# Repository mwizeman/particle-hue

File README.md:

# particle-hue
A remote set of buttons and knobs used to control Philips Hue lights

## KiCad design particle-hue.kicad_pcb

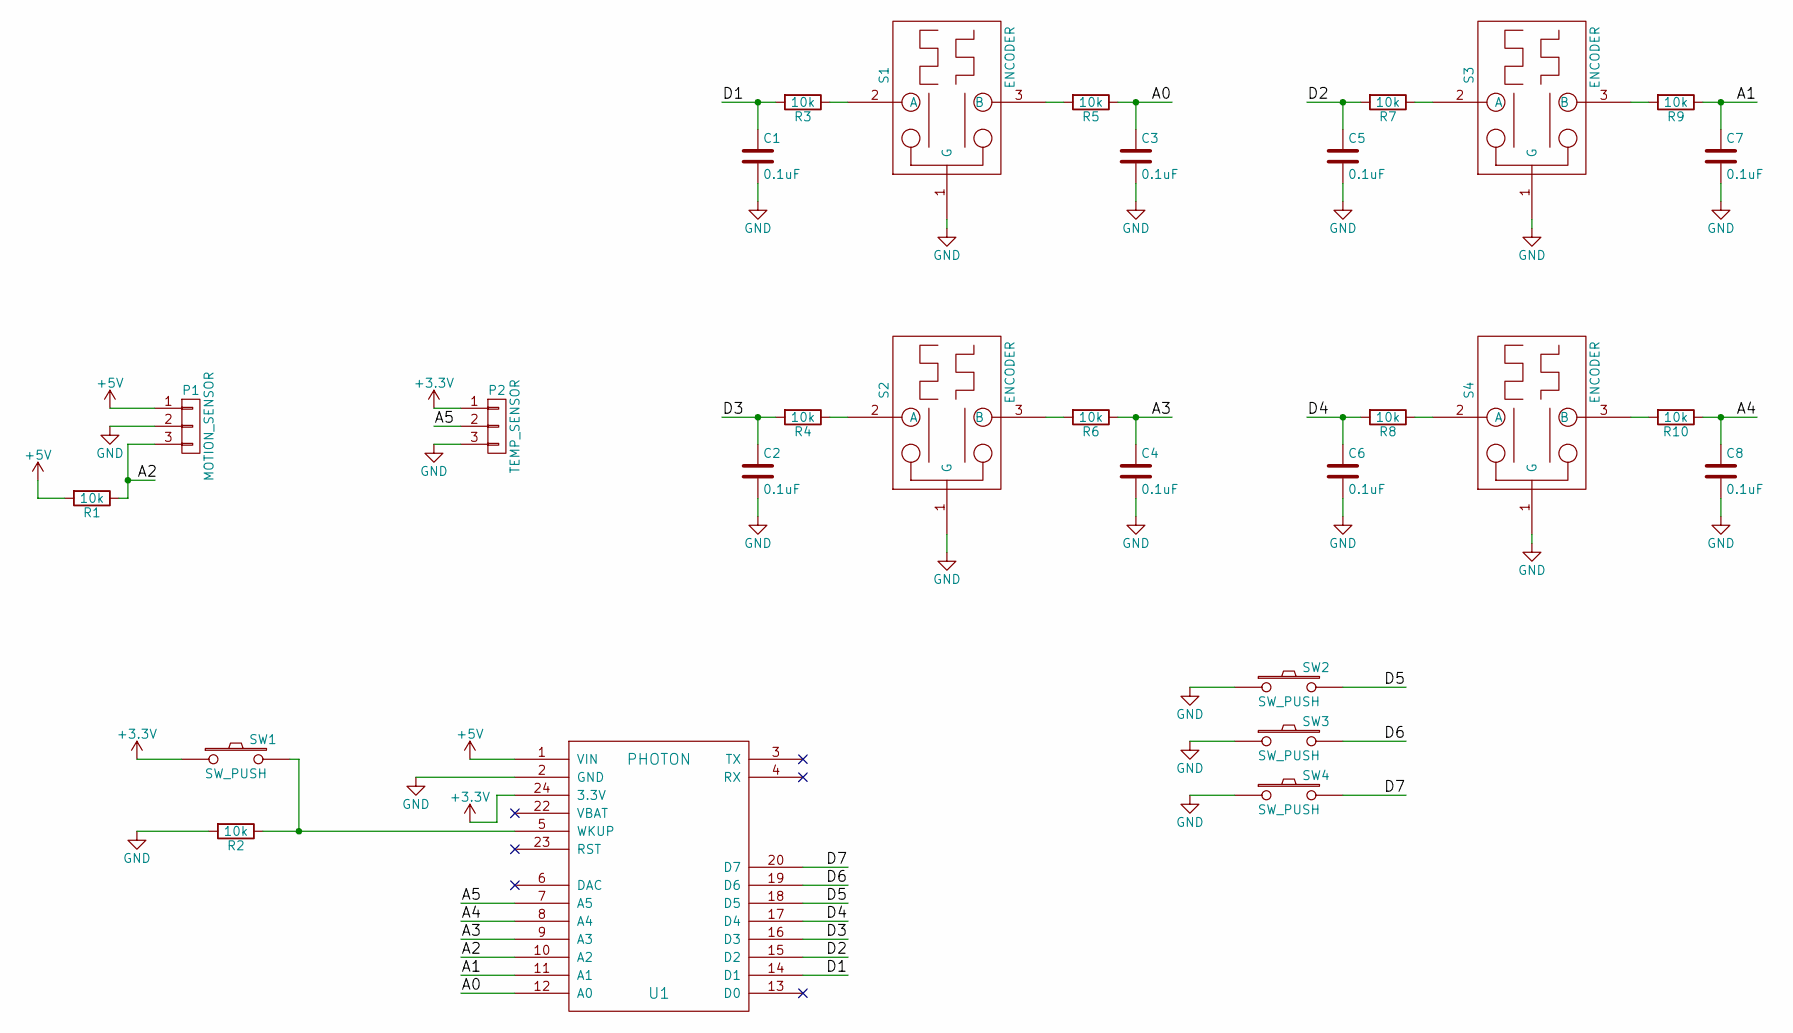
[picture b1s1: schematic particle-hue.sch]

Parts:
C1, C2, C3, C4, C5, C6, C7, C8: 0.1uF; C_Disc_D3_P2.5
P1: MOTION_SENSOR; Pin_Header_Straight_1x03
P2: TEMP_SENSOR; Pin_Header_Straight_1x03
R1, R2, R3, R4, R5, R6, R7, R8, R9, R10: 10k; Resistor_Horizontal_RM10mm
S1, S2, S3, S4: ENCODER; Pin_Header_Straight_1x03
SW1, SW2, SW3, SW4: SW_PUSH; Pin_Header_Straight_1x02
U1: PHOTON

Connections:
+3V3: P2.1, SW1.1, U1.24 (3.3V)
+5V: P1.1, R1.2, U1.1 (VIN)
/A0: C3.1, R5.1, U1.12 (A0)
/A1: C7.1, R9.1, U1.11 (A1)
/A2: P1.3, R1.1, U1.10 (A2)
/A3: C4.1, R6.1, U1.9 (A3)
/A4: C8.1, R10.1, U1.8 (A4)
/A5: P2.2, U1.7 (A5)
/D1: C1.1, R3.2, U1.14 (D1)
/D2: C5.1, R7.2, U1.15 (D2)
/D3: C2.1, R4.2, U1.16 (D3)
/D4: C6.1, R8.2, U1.17 (D4)
/D5: SW2.2, U1.18 (D5)
/D6: SW3.2, U1.19 (D6)
/D7: SW4.2, U1.20 (D7)
GND: C1.2, C2.2, C3.2, C4.2, C5.2, C6.2, C7.2, C8.2, P1.2, P2.3, R2.2, S1.1 (G), S2.1 (G), S3.1 (G), S4.1 (G), SW2.1, SW3.1, SW4.1, U1.2 (GND)
unnamed: R2.1, SW1.2, U1.5 (WKUP)
unnamed: R3.1, S1.2 (A)
unnamed: R4.1, S2.2 (A)
unnamed: R5.2, S1.3 (B)
unnamed: R6.2, S2.3 (B)
unnamed: R7.1, S3.2 (A)
unnamed: R8.1, S4.2 (A)
unnamed: R9.2, S3.3 (B)
unnamed: R10.2, S4.3 (B)

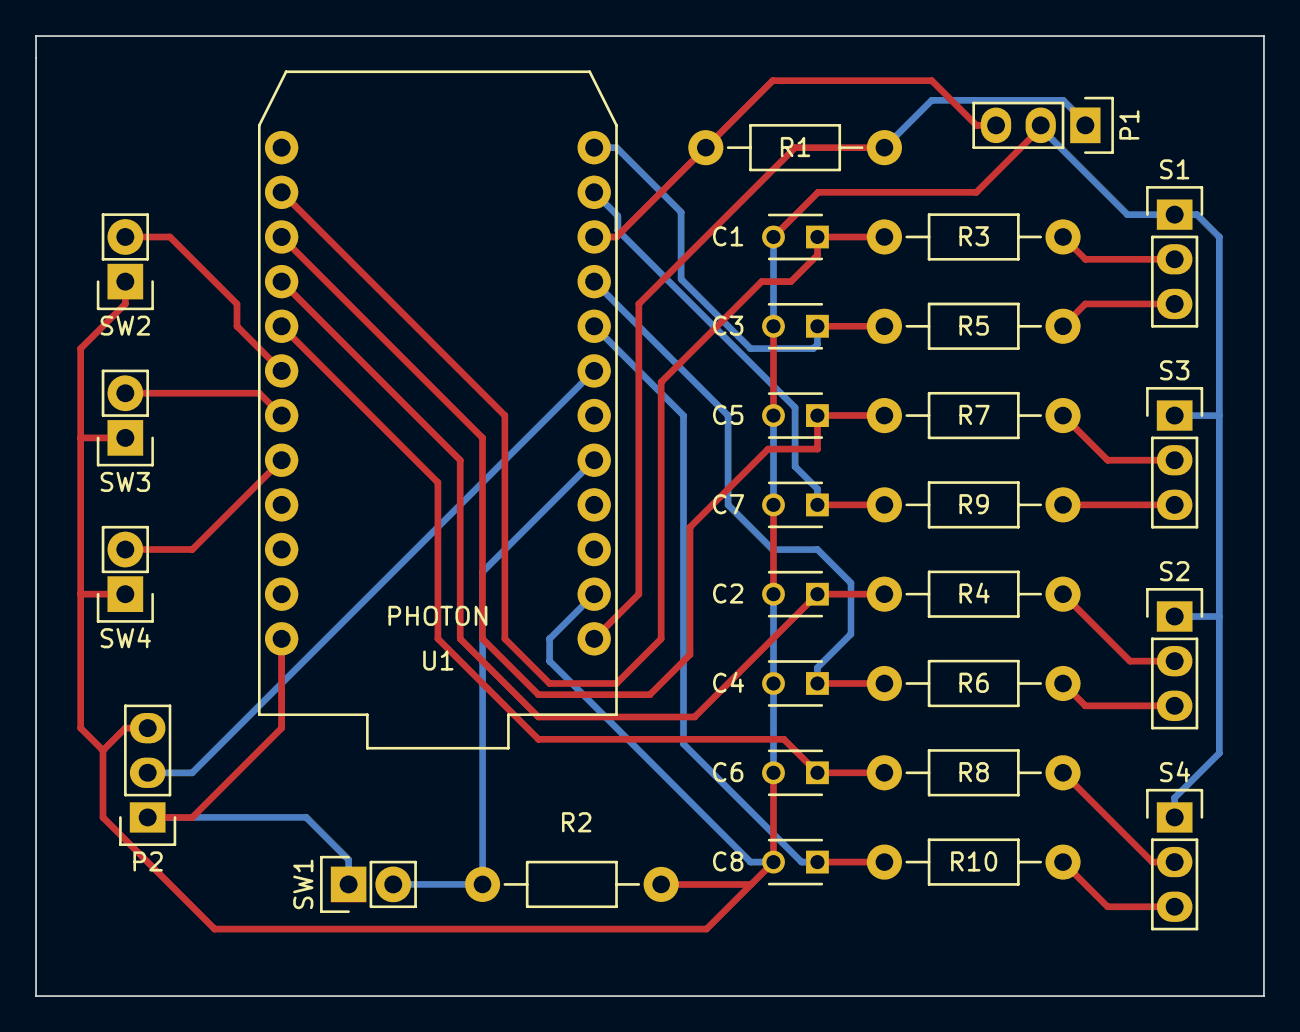
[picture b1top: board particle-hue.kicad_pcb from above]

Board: 2 copper layers, 69.9 x 54.6 mm, 29 parts (0 on the bottom side), 25 nets.

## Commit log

2016-01-27 updated to reflect some changes to the software
2016-01-31 updated the component numbers
2016-01-31 added the traces
2016-02-01 updates before sending v1 to OSH park
